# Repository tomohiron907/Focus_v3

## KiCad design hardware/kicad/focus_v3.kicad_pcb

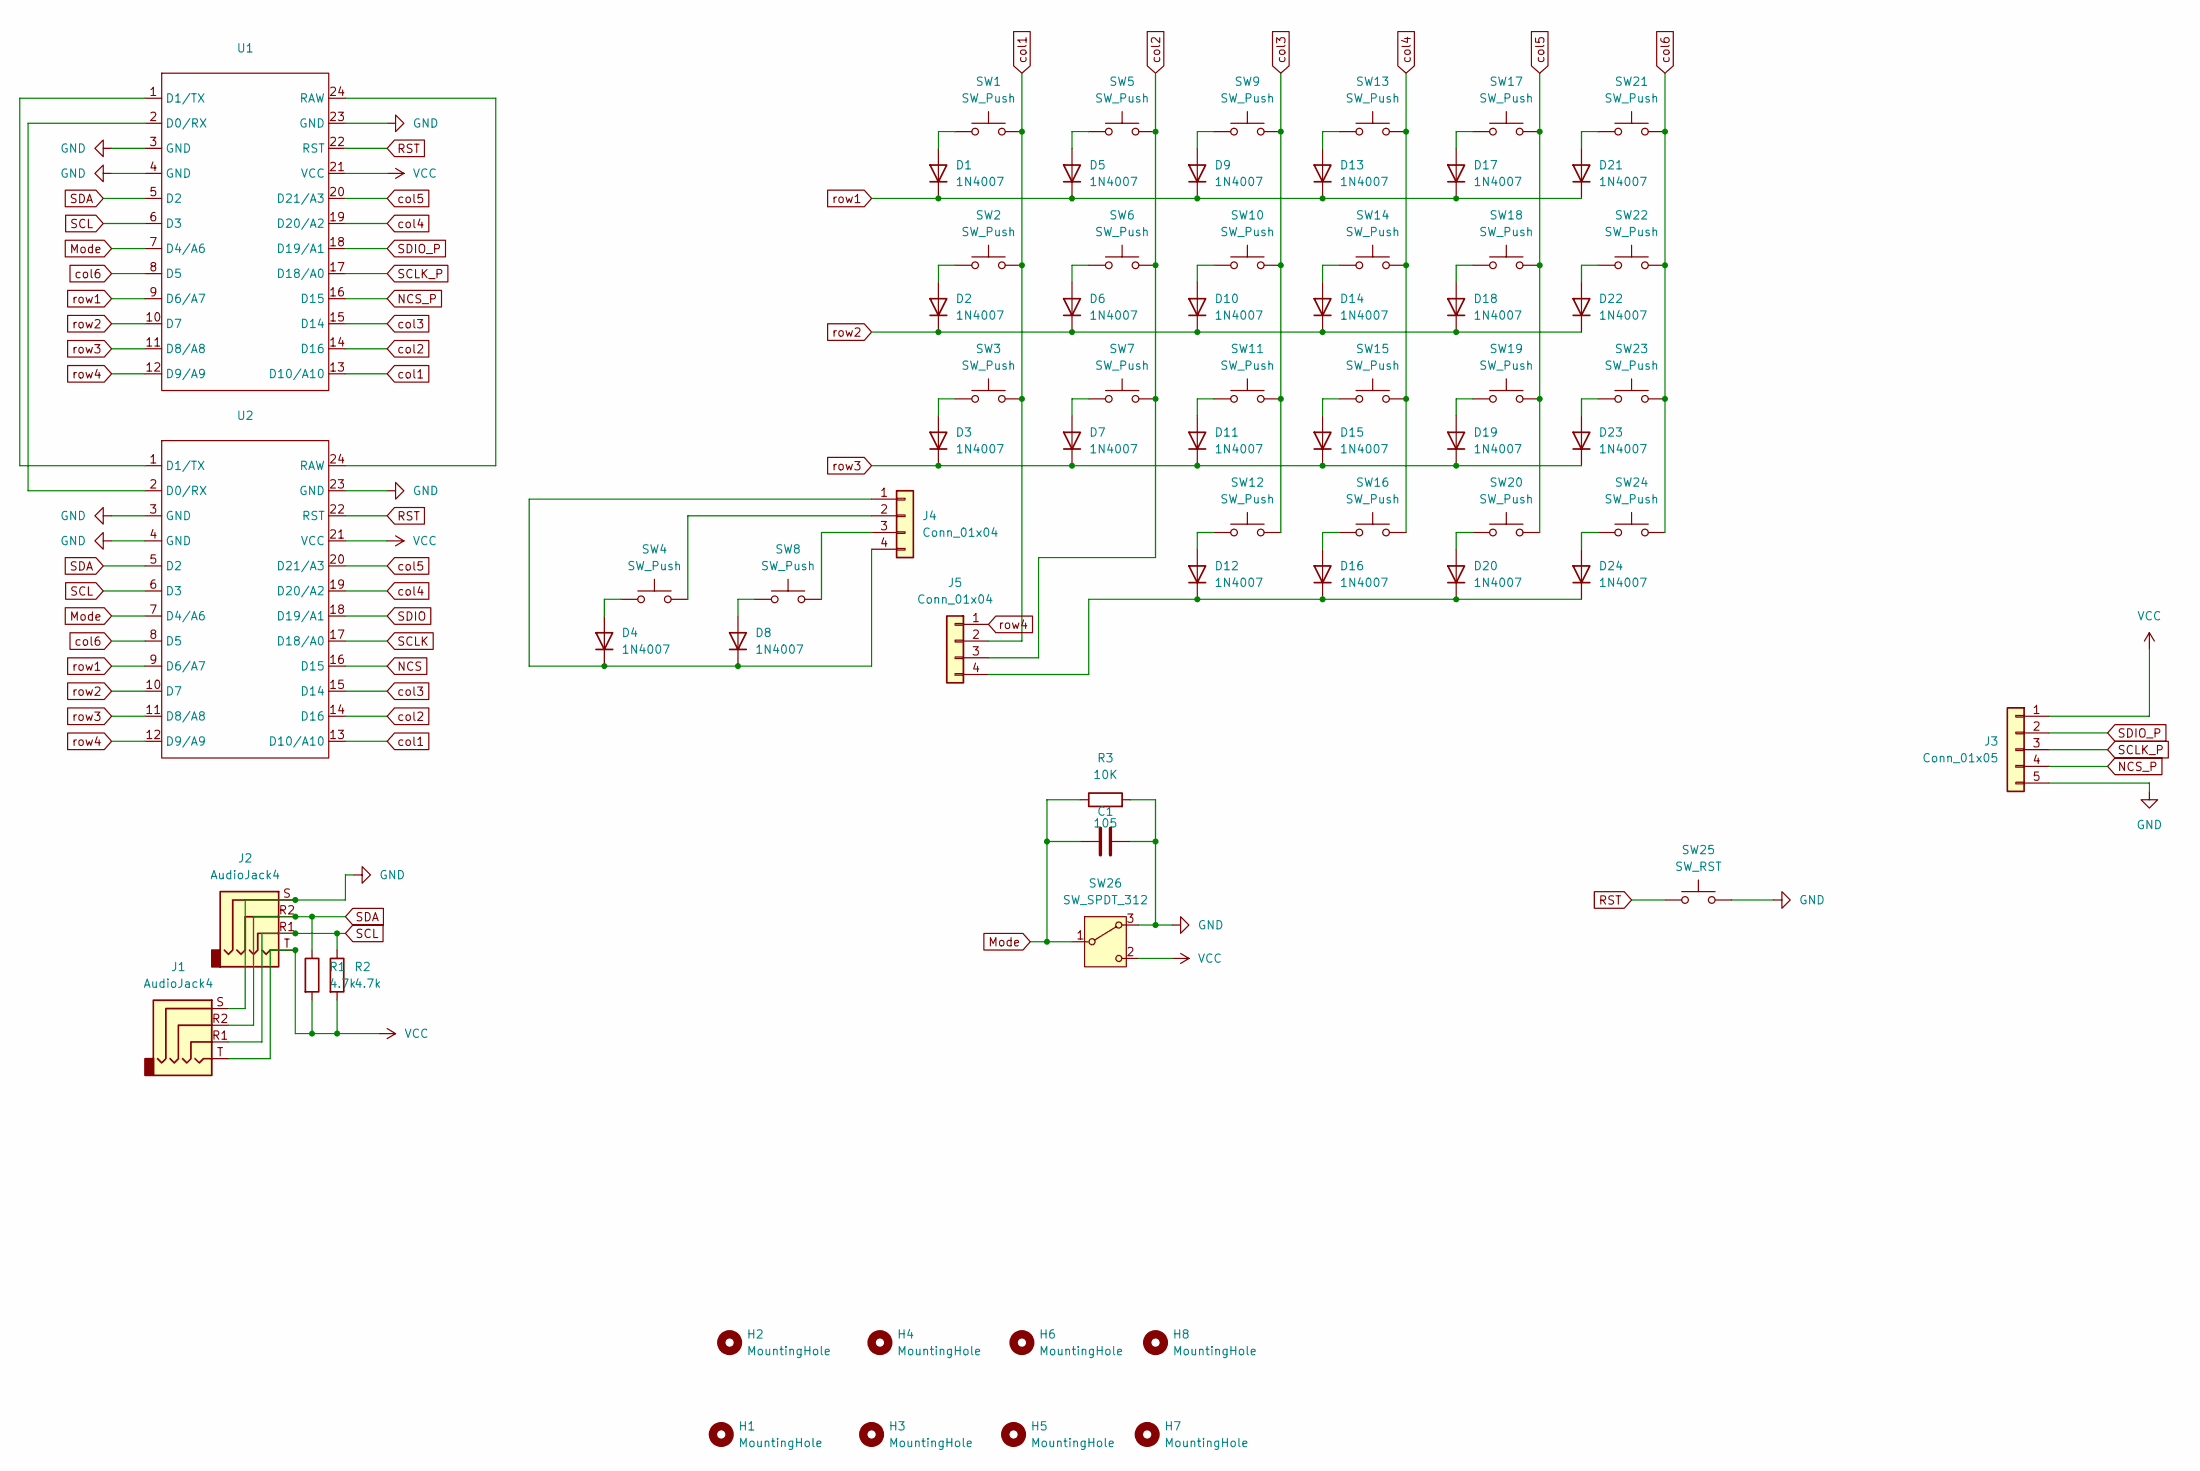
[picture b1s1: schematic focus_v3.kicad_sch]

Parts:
C1: 105; C_Disc_D5.0mm_W2.5mm_P5.00mm
D1, D2, D3, D4, D5, D6, D7, D8, D9, D10, D11, D12, D13, D14, D15, D16, D17, D18, D19, D20, D21, D22, D23, D24: 1N4007; D_T-1_P5.08mm_Horizontal
H1, H2, H3, H4, H5, H6, H7, H8: MountingHole; MountingHole_2.2mm_M2
J1, J2: AudioJack4; TRRS_Jack
J3: Conn_01x05; PinHeader_1x05_P2.54mm_Vertical
J4, J5: Conn_01x04; PinHeader_1x04_P2.54mm_Vertical
R1, R2: 4.7k; R_Axial_DIN0207_L6.3mm_D2.5mm_P10.16mm_Horizontal
R3: 10K; R_Axial_DIN0207_L6.3mm_D2.5mm_P10.16mm_Horizontal
SW1, SW2, SW3, SW4, SW5, SW6, SW7, SW8, SW9, SW10, SW11, SW12, SW13, SW14, SW15, SW16, SW17, SW18, SW19, SW20, SW21, SW22, SW23, SW24: SW_Push; Kailh_socket_PG1350_reversible
SW25: SW_RST; SW_PUSH_6mm_H4.3mm
SW26: SW_SPDT_312; vertical_slide_switch
U1, U2: ProMicro

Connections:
GND: C1.2, J1.S, J2.S, J3.5, R3.2, SW25.2, SW26.3 (A), U1.3 (GND), U1.4 (GND), U1.23 (GND), U2.3 (GND), U2.4 (GND), U2.23 (GND)
Mode: C1.1, R3.1, SW26.1 (B), U1.7 (D4/A6), U2.7 (D4/A6)
NCS: U2.16 (D15)
NCS_P: J3.4, U1.16 (D15)
unnamed: D1.2 (A), SW1.2
unnamed: D2.2 (A), SW2.2
unnamed: D3.2 (A), SW3.2
unnamed: D4.2 (A), SW4.2
unnamed: D4.1 (K), D8.1 (K), J4.1, J4.4
unnamed: D5.2 (A), SW5.2
unnamed: D6.2 (A), SW6.2
unnamed: D7.2 (A), SW7.2
unnamed: D8.2 (A), SW8.2
unnamed: D9.2 (A), SW9.2
unnamed: D10.2 (A), SW10.2
unnamed: D11.2 (A), SW11.2
unnamed: D12.2 (A), SW12.2
unnamed: D12.1 (K), D16.1 (K), D20.1 (K), D24.1 (K), J5.4
unnamed: D13.2 (A), SW13.2
unnamed: D14.2 (A), SW14.2
unnamed: D15.2 (A), SW15.2
unnamed: D16.2 (A), SW16.2
unnamed: D17.2 (A), SW17.2
unnamed: D18.2 (A), SW18.2
unnamed: D19.2 (A), SW19.2
unnamed: D20.2 (A), SW20.2
unnamed: D21.2 (A), SW21.2
unnamed: D22.2 (A), SW22.2
unnamed: D23.2 (A), SW23.2
unnamed: D24.2 (A), SW24.2
unnamed: J4.2, SW4.1
unnamed: J4.3, SW8.1
unnamed: U1.2 (D0/RX), U2.2 (D0/RX)
unnamed: U1.1 (D1/TX), U2.1 (D1/TX)
unnamed: U1.24 (RAW), U2.24 (RAW)
RST: SW25.1, U1.22 (RST), U2.22 (RST)
SCL: J1.R1, J2.R1, R2.1, U1.6 (D3), U2.6 (D3)
SCLK: U2.17 (D18/A0)
SCLK_P: J3.3, U1.17 (D18/A0)
SDA: J1.R2, J2.R2, R1.1, U1.5 (D2), U2.5 (D2)
SDIO: U2.18 (D19/A1)
SDIO_P: J3.2, U1.18 (D19/A1)
VCC: J1.T, J2.T, J3.1, R1.2, R2.2, SW26.2 (C), U1.21 (VCC), U2.21 (VCC)
col1: J5.2, SW1.1, SW2.1, SW3.1, U1.13 (D10/A10), U2.13 (D10/A10)
col2: J5.3, SW5.1, SW6.1, SW7.1, U1.14 (D16), U2.14 (D16)
col3: SW9.1, SW10.1, SW11.1, SW12.1, U1.15 (D14), U2.15 (D14)
col4: SW13.1, SW14.1, SW15.1, SW16.1, U1.19 (D20/A2), U2.19 (D20/A2)
col5: SW17.1, SW18.1, SW19.1, SW20.1, U1.20 (D21/A3), U2.20 (D21/A3)
col6: SW21.1, SW22.1, SW23.1, SW24.1, U1.8 (D5), U2.8 (D5)
row1: D1.1 (K), D5.1 (K), D9.1 (K), D13.1 (K), D17.1 (K), D21.1 (K), U1.9 (D6/A7), U2.9 (D6/A7)
row2: D2.1 (K), D6.1 (K), D10.1 (K), D14.1 (K), D18.1 (K), D22.1 (K), U1.10 (D7), U2.10 (D7)
row3: D3.1 (K), D7.1 (K), D11.1 (K), D15.1 (K), D19.1 (K), D23.1 (K), U1.11 (D8/A8), U2.11 (D8/A8)
row4: J5.1, U1.12 (D9/A9), U2.12 (D9/A9)

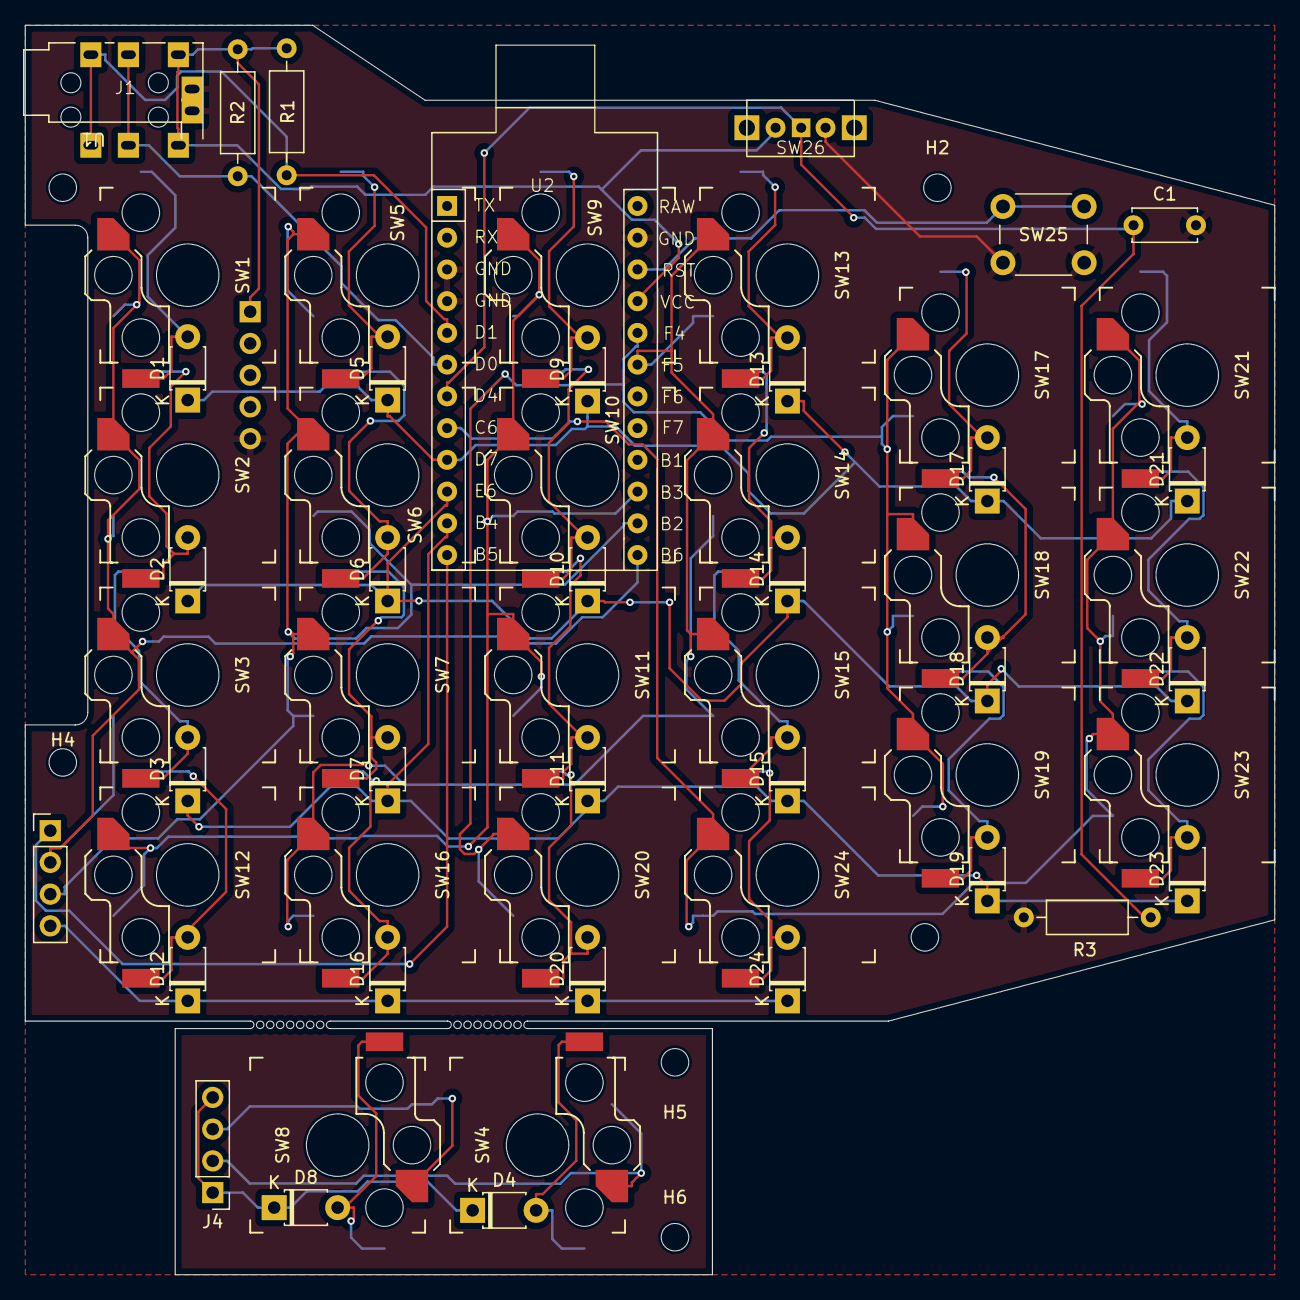
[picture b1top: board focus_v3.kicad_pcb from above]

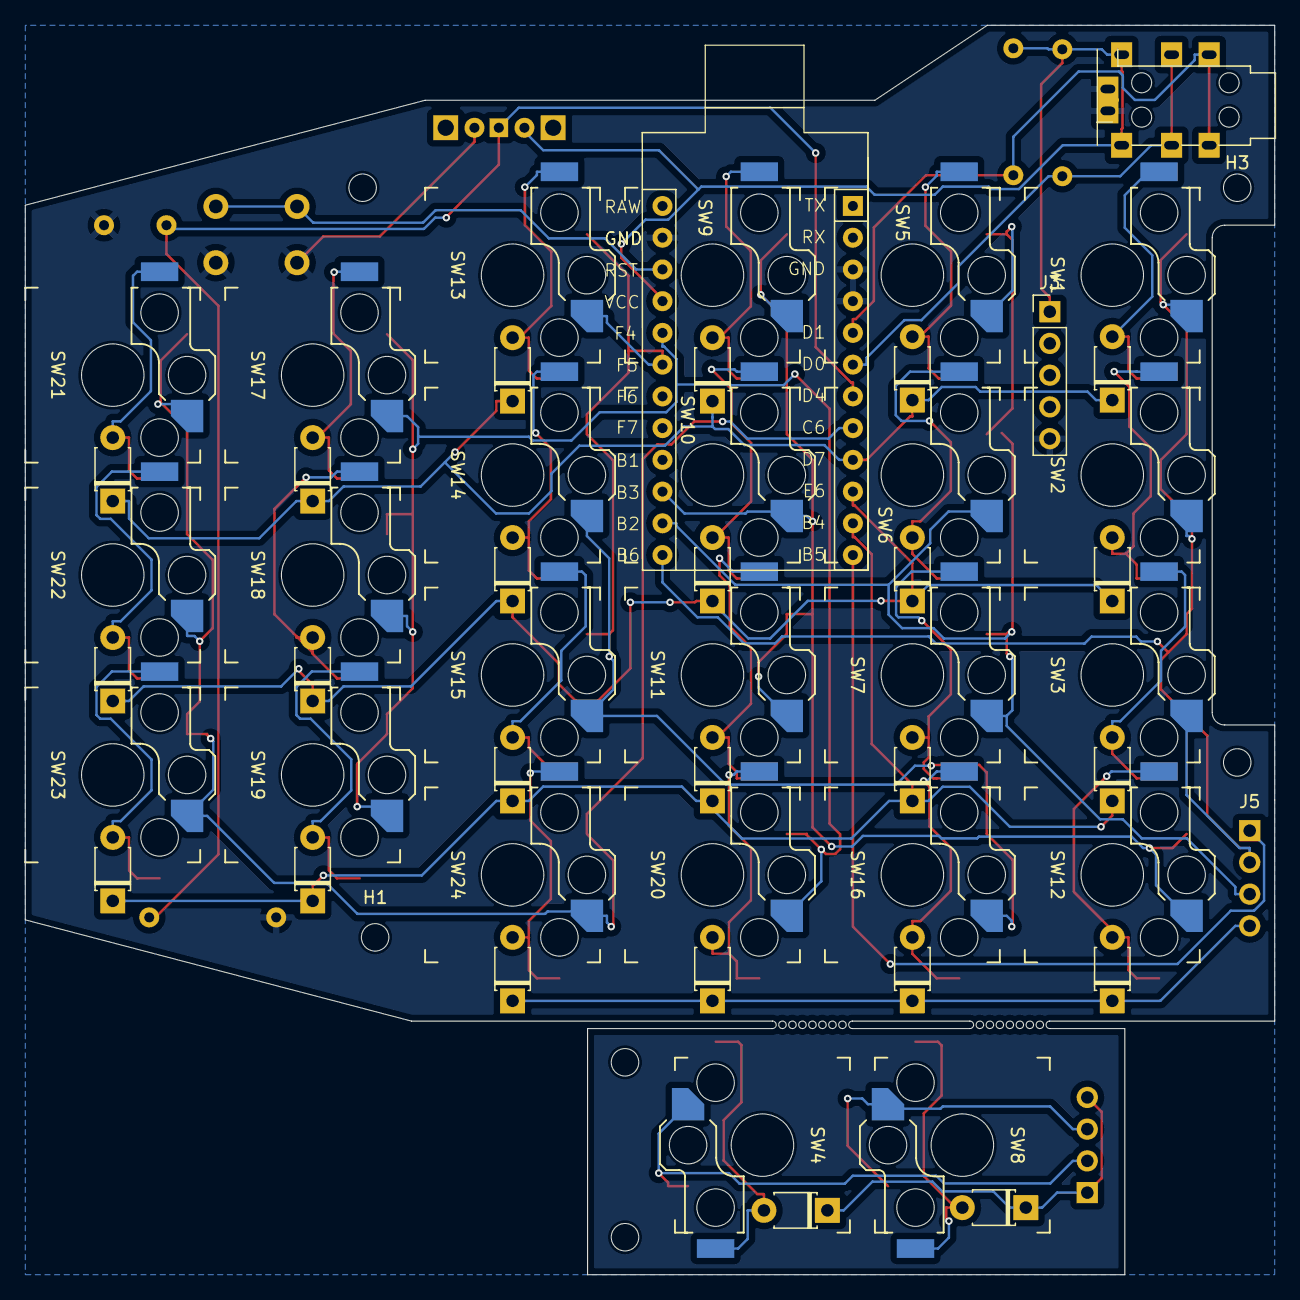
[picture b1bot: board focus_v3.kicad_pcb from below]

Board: 2 copper layers, 100.0 x 100.0 mm, 67 parts (8 on the bottom side), 44 nets.

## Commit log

2025-11-01 add hardware files
2025-11-01 add firmware
2025-11-01 move keymap.c into keymap directory
2025-11-02 add gesture for move virtual desktop
2025-11-02 enabled continuous gesture movement
2025-11-15 update keymappings
